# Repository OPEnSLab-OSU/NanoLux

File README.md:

# Nanolux
Cymaspace [Audiolux](https://www.cymaspace.org/audiolux/) Opensource code

The Audiolux device is a product developed by Portland-based company CymaSpace that visualizes music or other performing arts on LED strips, enabling the deaf and hard of hearing to participate in these events. The Audiolux device is a pre-existing product, so the goal of this project is to make improvements such as adding user configurable modes, increasing the number of visualization patterns on the LEDs, making configuration wireless, and improving accuracy of pitch detection.

#### Please check out our [Wiki](https://github.com/OPEnSLab-OSU/Nanolux/wiki) for more user info and documentation.

# Install the Arduino Desktop IDE
Dev environment:
* To get step-by-step instructions select one of the following link accordingly to your operating system.

Windows (http://docs.arduino.cc/software/ide-v1/tutorials/Windows)

Mac OS (http://docs.arduino.cc/software/ide-v1/tutorials/macOS)

Linux (http://docs.arduino.cc/software/ide-v1/tutorials/Linux)

## Dependencies

### 1. Using the **`dependencies`** branch (Recommended)
We have bundled all of the manually required libraries into a single `libraries/` folder on the **`dependencies`** branch. That way, you don’t have to install each one by hand. See the next section if you want/need to manually install them.

1. **Clone (or fetch) the repo and switch to `dependencies`:**
   ```bash
   git clone https://github.com/OPEnSLab-OSU/Nanolux.git
   cd Nanolux
   git fetch origin
   git checkout dependencies
   ```
2. **Locate the `libraries/` folder** at the root of this branch. It contains:
   - ESPAsyncWebServer (v1.2.3)
   - AsyncTCP (v1.1.4)
   - AudioPrism
   - All other custom or manually‑required libraries as seen in the next section
3. **Copy (or symlink) that `libraries/` folder into your Arduino sketchbook’s “libraries” directory.**  
   - On Windows, your sketchbook is usually:  
     ```
     C:\Users\<YourUserName>\Documents\Arduino\libraries
     ```
   - On macOS/Linux, it’s typically:  
     ```
     ~/Arduino/libraries
     ```
   For example:
   ```bash
   # if your sketchbook is ~/Arduino
   cp -r libraries ~/Arduino/
   ```

   Once that’s done, Arduino IDE will automatically pick up those libraries the next time you open it.

4. **Switch back to `main` (if you want to compile/upload the main firmware):**
   ```bash
   git checkout main
   ```
   Because your `main/` folder references those libraries by name, Arduino can now find them.

### 2. Installing via Arduino IDE / Library Manager (Alternate)
You will also need several libraries. See the [IDE Setup Guide](https://github.com/OPEnSLab-OSU/Nanolux/wiki/Arduino-IDE-Setting-Guide) Wiki Page for steps on how to install these libraries.

- Ai ESP32 Rotary Encoder (1.6)
- ArduinoJson (7.1.0)
- FastLED (3.7.0)
- fast4ier (1.0.0)
- ESP32 Board Library (2.0.17)

All dependencies above are installable through the Library Manager of the Arduino IDE, or with the 
[Arduino CLI](https://arduino.github.io/arduino-cli/0.28/) tool.

The following dependencies must be installed manually. Refer to Wiki for more info.

* ESPAsynWebServer (1.2.3): https://github.com/me-no-dev/ESPAsyncWebServer
* AsyncTCP (1.1.4): https://github.com/me-no-dev/AsyncTCP
* AudioPrism: https://github.com/udellc/AudioPrism

# Install Board
You will need to install the ESP32 board driver for developing on this board.
* Install ESP32 Board: https://www.hackster.io/abdularbi17/how-to-install-esp32-board-in-arduino-ide-1cd571
You will also need to check the port connection with ESP32 Board.
* Serial Connection with ESP32: https://docs.espressif.com/projects/esp-idf/en/latest/esp32/get-started/establish-serial-connection.html

Use the “ESP32” package by Espressif Systems at version 2.0.16. In Arduino IDE, open Tools → Board → Boards Manager, search for “esp32,” and install or roll back to esp32 by Espressif Systems v2.0.16. This version is required to compile FastLED 3.7.0 without errors.

# Using the AudioLux Device
Once the device is set up correctly, it can be powered on using its micro USB and fed audio through the 3.5mm audio jack. To configure the device, either use the rotary encoder to cycle through patterns and modes or use the AudioLux web app (ensure the web application is deployed by following these steps in the Wiki: [The Web App](https://github.com/OPEnSLab-OSU/Nanolux/wiki/The-Web-App)). Once deployed by the device, the web app can be connected to by opening your device's Wifi settings and selecting the AudioLux Wifi (`AudioluxUnsecured`) that is hosted by the AudioLux device, and then opening the web app by going to `http://192.168.4.1/` if the device has not been configured before or `http://audiolux.local` if the device has been configured. Once connected, the AudioLux device can be configured freely using all of the web app's functionality and/or the device's rotary encoder.

# Some Important Things To Note

1. The most up to date stable release is located in the [Main](https://github.com/OPEnSLab-OSU/Nanolux/tree/main/main) directory. 
This is the code that should be uploaded to the device. Make sure to follow the Web App Wiki to upload the code
needed to run the Web App.

2. If you wish to disable the webapp, you can comment out the flag "ENABLE_WEB_SERVER". Make note to which analog ports are being used,
disabling the webapp however should not give a boost in performance, given that the webapp is asynch and on a seperate core.

---

# Contributors
2021-2022 Team:

John Zontos (zontosj@oregonstate.edu)

Evan Cochran (cochraev@oregonstate.edu)

Longjie Guan (guanl@oregonstate.edu)

Ming Wei (weimi@oregonstate.edu)

2022-2023 Team:

Andrew Gingerich (gingeria@oregonstate.edu)

Luke Goldsworthy (goldswol@oregonstate.edu)

Mac Handley (handlem@oregonstate.edu)

Vishnu Kalidas (kalidasv@oregonstate.edu)

Jorden Mortenson (mortejor@oregonstate.edu)

David Mora (morad@oregonstate.edu)

2023-2024 Team:

Andrew Adisoemarta (adisoema@oregonstate.edu)

Anshul Batish (batisha@oregonstate.edu)

Caleb Shilling (shillinc@oregonstate.edu)

Can Yang (yangca@oregonstate.edu)

Scout Hawkey (hawkeys@oregonstate.edu)

2024-2025 Team:

Andrew Craeton (craetona@oregonstate.edu)

Theodore Ngo (ngoth@oregonstate.edu)

Matthew Manuguid (manuguim@oregonstate.edu)

Nicholas Wooldridge (wooldrni@oregonstate.edu)

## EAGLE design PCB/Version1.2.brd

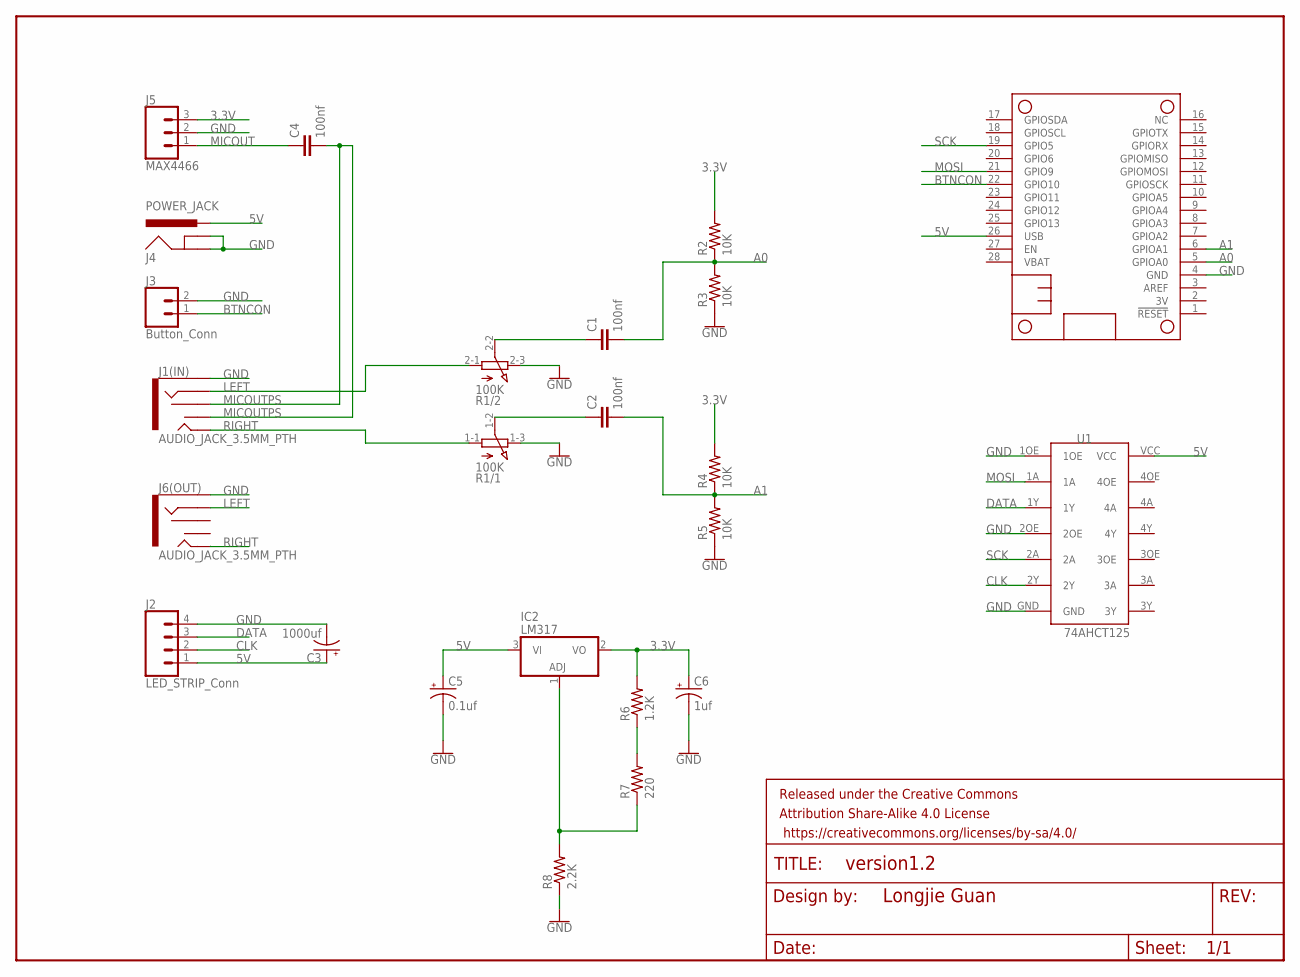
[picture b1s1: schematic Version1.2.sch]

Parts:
C1, C2, C4: 100nf; C2.5-2
C3: 1000uf; B45181A
C5: 0.1uf; B45181A
C6: 1uf; B45181A
FRAME1: FRAME-LETTERNO_PACKAGE; DUMMY
IC2: LM317; TO220H
J1(IN), J6(OUT): AUDIO_JACK_3.5MM_PTH; AUDIO-JACK
J2: LED_STRIP_Conn; 1X04_LOCK
J3: Button_Conn; 1X02
J4: POWER_JACK; POWER_JACK_PTH
J5: MAX4466; 1X03
MS1: FEATHERWING_NODIM; FEATHERWING_DIM
R1: 100K; 3RP/1610G
R2, R3, R4, R5: 10K; 0204/7
R6: 1.2K; 0204/7
R7: 220; 0204/7
R8: 2.2K; 0204/7
U1: 74AHCT125; 74AHCT125FP

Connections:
3.3V: C6.+, IC2.2 (VO), J5.3, R2.2, R4.2, R6.2
5V: C3.+, C5.+, IC2.3 (VI), J2.1, J4.PWR, MS1.26 (USB), U1.VCC
A0: C1.2, MS1.5 (GPIOA0), R2.1, R3.2
A1: C2.2, MS1.6 (GPIOA1), R4.1, R5.2
BTNCON: J3.1, MS1.22 (GPIO10)
CLK: J2.2, U1.2Y
DATA: J2.3, U1.1Y
GND: C3.-, C5.-, C6.-, J1(IN).SLEEVE, J2.4, J3.2, J4.GND, J4.GNDBREAK, J5.2, J6(OUT).SLEEVE, MS1.4 (GND), R1.1-3 (E), R1.2-3 (E), R3.1, R5.1, R8.1, U1.1OE, U1.2OE, U1.GND
LEFT: J1(IN).RING, J6(OUT).RING, R1.2-1 (A)
MICOUT: C4.1, J5.1
MICOUTPS: C4.2, J1(IN).RSH, J1(IN).TSH
MOSI: MS1.21 (GPIO9), U1.1A
unnamed: C1.1, R1.2-2 (S)
unnamed: C2.1, R1.1-2 (S)
unnamed: R6.1, R7.2
unnamed: IC2.1 (ADJ), R7.1, R8.2
RIGHT: J1(IN).TIP, J6(OUT).TIP, R1.1-1 (A)
SCK: MS1.19 (GPIO5), U1.2A

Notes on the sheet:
Longjie Guan

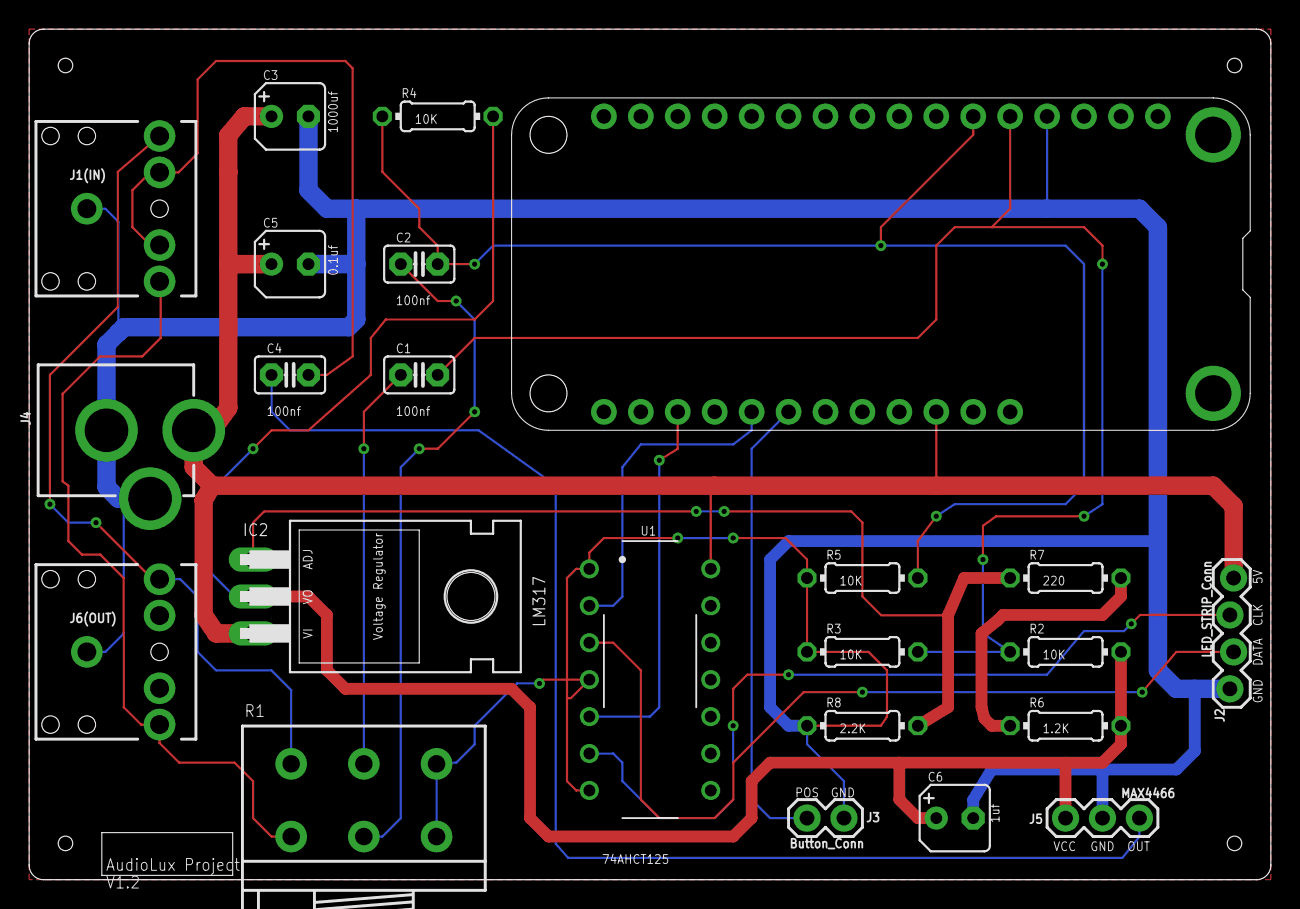
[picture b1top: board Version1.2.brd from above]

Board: 2 copper layers, 85.4 x 58.5 mm, 24 parts (0 on the bottom side), 18 nets.

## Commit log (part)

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2023-12-07 check in
2023-12-07 Save selector UI functional
2023-12-08 Pattern saving complete, web app fixes
2023-12-08 Bugfix: fastLED.clear calls replaced in patterns.cpp with clearLEDSegment()
2023-12-10 Revert "Revert "Merge branch 'simulator' into 2.1.0_unstable""
    This reverts commit 2b6c89d82d19b7e44578e273b65ad534119fa39b.
2023-12-10 Manual merge of previous Simulator branch push
2023-12-11 Fixed strip stopping after 2 seconds
    Added sanity check that pix and vol position does not go over NUM_LEDS
2023-12-13 Simulator readme revision
2023-12-15 Changes to echo ripple
    New todos:
    1. make it asynch with an FSM
    2. get audio jack from home to get the colors and distance working according to the music
2023-12-20 Added the ability to reset saved patterns using the device momentary switch.
2023-12-23 Added the ability to change the smoothing constant and brightness on the web app.
2024-01-09 temp push to work elsewhere.
2024-01-19 formant colors + blending
    Added color blend to the ripples when they collide
2024-01-19 colorful blend
    added changes so that less white is seen when blending/expanding
2024-01-19 modifies
2024-01-19 Added the ability to change the LED strip length on the UI and began fixing issue with UI not updating on occasion.
2024-01-24 added bg pic & changed CSS
2024-01-25 Fixed config data not saving to NVS
2024-02-01 Pattern functions now have paramenters for pattern history pointer and # of addressed LEDs.
2024-02-01 Fixed simulator using the non-smoothed output buffer and moved sim output to after smoothing calculation.
2024-02-02 echo ripple debugging
    testing fixes to implement a new echo ripple into unstable
2024-02-07 check-in
2024-02-08 check-in, laptop-desktop merge
2024-02-08 functional strip splitting
2024-02-09 Style changed
2024-02-10 Update mockapi_dqm_audioluxmockapi.yml
    Added autoformatting action
2024-02-10 Create clang_autoformat.yml
    added clang to a separate workflow
2024-02-10 Update clang_autoformat.yml
    fix to source files in format action
2024-02-10 added to gitignore
2024-02-10 updated clang action
2024-02-13 Brightness and smoothing per-subpattern reimplemented. Fixed bug with getting current subpattern data correctly.
2024-02-14 Monday check-in commit
2024-02-15 6 Major Pattern Functions
    Completed implementation in main, patterns.cpp/h, storage accessing work in progress NOT TESTED
2024-02-16 pattern header file changes
2024-02-16 Feature parity with unstable
2024-02-22 Updated UI CSS
2024-02-22 processDirection function implemented NOTTESTED
    need to add sanity checks
2024-02-23 updtas
2024-02-23 Compile fixes
2024-02-23 Compilation fix
2024-02-26 Added bound checking to API inputs and pattern loading/saving. Untested.
2024-02-27 Bugfixes for byte bounding function parameters and verified manual control mode
2024-03-01 Finished up tug of war functions
    Added volume and frequency tug of war
2024-03-01 Bugfixes and Doxygen comments
2024-03-06 Compile fixes
    Compiles now yay
2024-03-06 Added drop down for config selector.
2024-03-08 quick push
    new fhue and vbrightness
2024-03-08 Tug o' war and Raindrop patterns
    Added two new patterns with variations on the Tug O' War pattern
2024-03-14 Added API calls to change device name and password, added capability to rename device through serial
2024-03-15 Added SSID and password resetting
2024-04-08 Updated documentation
2024-04-08 empty commit, ready for pages
2024-04-08 doxygen manual test
2024-04-08 check-in commit
2024-04-15 Additional docs added
2024-04-15 Adding html page to perform automatic redirection to docs page.
2024-04-19 Doxygen build test
2024-04-19 doxyfile path fix
2024-04-19 deploy: f7f140341c393304e3905966bd094f25c675b375
2024-04-26 Minor update to force pages update
2024-04-26 deploy: f95bdb87bdc83ba005b5b226671c5cdfb19960b8
2024-04-26 deploy: a34a3394f9fe11a0b3b479002ac79991e03a6701
2024-04-26 attempted doxygen update
2024-04-26 deploy: 1f20743fa51dfe23f257cb24146e107d81bc3ecc
2024-04-29 Web app doxyfile and docs changes
2024-04-29 multi-docs attempt 2
2024-04-29 Removed double checkout in Actions
2024-04-29 Removed extra deploy
2024-04-29 deploy: 891d87bd7f26f0a0c6fc35927c7b88b2c140e968
2024-04-29 deploy: 1fdf2683764086d5ef4cc9a97251e66e11246d3e
2024-04-29 deploy: 5cd4fd70c269af92dc06b0410e0ca24ca34fd8b7
2024-05-06 Initial project renaming commit
2024-05-06 Alpha manual pushed, direction feedback needed
2024-05-08 Added a new subpattern data option for postprocessing effects.
2024-05-10 added rotary encoder code
2024-05-10 Working Code
2024-05-10 Web app doxygen fixes
2024-05-12 deploy: e8e0d4384e4ef1c7ed0590510e6288174414762e
2024-05-12 Modified postprocessing effects to use an integer instead of a boolean
2024-05-13 Bigfixes, ready to merge to prerelease
2024-05-13 rotaryEncoder
2024-05-13 deploy: d6877395646266dfd1e3029916e6b487dff88454
2024-05-13 deploy: ebc9a2d244259ce48ddf4b7392078a4b47fdd68e
2024-05-13 deploy: a6ec5bcd6b86a8b0d4232526484bcb968ff37591
2024-05-17 Create file
2024-05-17 Revert "Merge branch '3.0.0_prerelease' of https://github.com/OPEnSLab-OSU/Nanolux into 3.0.0_prerelease"
    This reverts commit a6a5350838db440ca9f1dd9ba14bd06c03140976, reversing
    changes made to 9996c730e3e58d8137f5343e3fc6eb7463fdb04b.
2024-05-17 deploy: 2194b1bccd1e08740f93f9c4c0dee63de07fb0f3
2024-05-17 deploy: b877bdbfc1859840259719a0bf2cd152b2a3f58a
2024-05-17 deploy: 0cfd07c08b23ac1bc4633db8edc3a45a4ca2ee18
2024-05-17 removed extra deploy steps
2024-05-18 Added landing page and moved old folders to "archive" before potential removal
2024-05-18 deploy: 99b6abca77e2158ae7b82c3f0a7f0a978e1e1e91
2024-05-18 deploy: e185ffc2e5fda6504a0ad0fb1dd6f5dba0a2bf60
2024-05-18 deploy: 60f0ad9f57ea9af17fa63f838cdf462b4ce79a50
2024-05-20 Re-implemented manual mode, temporary crash prevention on bands pattern
2024-05-20 Ready for merge.
2024-05-20 deploy: 54ab0f8d7db833eef20664a577c1daba0a8f55ad
2024-05-20 Uploading manual files
2024-05-20 vowel detection
    Added vowel detection to the newest prerelease
2024-05-20 saturated and groovy fix *not tested*
2024-05-22 Manual 1.0 release, additional manual pages, manual build script, new Bar Fill pattern
2024-05-23 updated vowel detection
    ^
2024-05-23 removed/updated old comment
2024-05-24 Fixed postprocess being a boolean
2024-05-24 deploy: 9156750487f472cc3ad2036702db24e92c02540c
2024-05-24 deploy: d7d0fa99a73f935e9fb425e4dc48de33d1a4a4d5
2024-05-24 deploy: 5c711aad61e23256cfecdc3031a9d13b91ac99e4
2024-05-24 Current pattern on UI now decreases when the viewed one is removed
2024-05-25 Minor docs changes, removal of old functions
2024-05-25 deploy: 088f2dd2dadbc42a36791ff2c95bc1a1d40bfd2e
2024-05-27 deploy: bc0de6fb54247915f35cd535bd10570d5aeff467
2024-06-02 deploy: 52b1d48014b2c4b3f8da646af4b15aae977b8ed4
2024-06-02 Added clean command to npm
2024-06-02 Update README.md
    Added the 2023-2024 dev team
2024-06-02 deploy: ac50dacd284c3b173ce7d6e379cd1e72cebf2b9f
2024-06-02 deploy: 390a1d530bc5f03b499299107de0e72f9bbf62bb
2024-06-24 Fixes to software AP mDNS, expanded smoothing range, simplified postprocessing mode selection
2024-06-26 Fix to rotary encoder, removed encoder button calls
2024-06-28 Disabled SD Loader by default
2024-06-29 deploy: 777058139534b63654c534eac946d8d599dfe89c
2024-07-29 Simulator V3 Prerelease
2024-12-04 Adjusted rotary encoder upper boundary and removed modulo logic due to redundancy
2024-12-04 modified core analysis to demo audioprism integration
2025-01-29 core_analysis functions replaced by audioprism modules
2025-01-30 Added functionality and logic for encoder bidirectionality with web app
2025-01-31 ensureing audio analysis files compile
2025-02-05 enabled SD card and added print statements to debug encoder value updates
2025-02-19 fully implemented bidirectional communication from encoder to pattern selection UI in webapp
2025-02-27 pattern_test
2025-02-28 correcting type issues in legacy code
2025-02-28 Commit to prep for adding new patterns
2025-02-28 fix to previous commit
2025-02-28 note testing
2025-02-28 note fixes
2025-03-07 Added noteEQ pattern
2025-03-07 optimized and fixed noteEQ
2025-03-07 Improvements to synesthesia fading
2025-03-07 Fixed delta functionality
2025-03-11 Added rainbow slider and modified patterns component
2025-03-11 modified css file for multirange slider component
2025-04-15 Removal of rainbow slider from pattern_settings, modified rainbow slider component, adjusted all settings components to include tooltips, added new dependency to project
2025-04-15 updated spacing, multi-range-slider dependency, color palette, and deleted redundant css files
2025-04-15 readded padding-top to main app
2025-04-22 Modified CSS for Settings page components to increase sizing, align color schemes, and space elements properly
2025-04-25 verified multi window analysis functions functionality
2025-04-26 transistioned to new analysis loop in patterns. deleted previous AA files
2025-05-02 styled wifi page to match settings page and swapped the config imported dropdown with a select element to style it the same as current pattern
2025-05-06 implemented UI color themes and a toggle for basic/advanced settings page
2025-05-09 Modified settings index.js files
2025-05-13 ensure loaded_pattern attributes from rotary encoder stay uint64
2025-05-16 Added 2024-2025 team to README.md
2025-05-16 deploy: c1efa2eded04c2b0ad85c92a57e05226867cde0c
2025-05-20 styled tooltip popups, added tooltips to SimpleChooser options, adjusted tooltip descriptions, refactored and restyled pattern modal for future dev
2025-05-24 fully removed manual_pattern and VERSION_2_HARDWARE and LittleFS macro logic
2025-05-24 moved to fast4ier
2025-05-24 fixed type issues casued by mergeing new patterns
2025-05-24 deploy: 06f1993747c40e9596c4e4d5e0e46a08c346d2fc
2025-05-25 Update README.md
    Added End-User Instructions
2025-05-27 added screen reader compatibility with ARIA
2025-05-27 updated size-plugin.json from npm run build
2025-05-28 testing changes to fft loop
2025-05-28 changes verified - FTT works
2025-05-28 simplified AP init
2025-05-30 resolved lint and Lighthouse issues
2025-05-30 add GitHub actions for ESLint a11y and Lighthouse CI
2025-05-30 remove Windows-only clean script from Lighthouse config and update Node version in GitHub Actions
2025-05-30 modified GitHub actions scope for lighthouse and lint to only run on changes inside WebApp
2025-05-31 deploy: 5660dfe0f4278995971c82eab45bc783ff898829
2025-06-01 updated markdown files for frontend and rotary encoder changes
2025-06-01 fixed comment typo in loop()
2025-06-01 updated/ added jsdoc comments to new and modified components for doxygen build
2025-06-01 update doxygen to grant write permissions
2025-06-01 removed running doxygen on PRs (no write permissions)
2025-06-01 added optional categories to the lighthouse config
2025-06-01 deploy: 3693334008dcbd6e2af82f7976f0607575dc1d45
2025-06-01 increased analysis functionality
2025-06-02 analysis changes
2025-06-02 added doxygen comments
2025-06-02 deploy: 3b99eec53f2a7612261ea4c06b92398f448320fd
2025-06-02 removed old dependency reference
2025-06-02 deploy: 217a24fe27d7673510b43eb8aaadfb9acbe763a7
2025-06-02 deploy: 557227b24b2b495f88e7c3a4f2abd4c7d14edb8a
2025-06-02 deploy: 75d62b045dcc17e12eb549a0f80dd202f4e35e2a
2025-06-02 deploy: 82866e60f4b0b35700e8b83d6bafccb4b726d636
2025-06-02 deploy: 66bee14ed602e39b77d9191e75f7a00f12de28fd
2025-06-02 hopefully this is good
2025-06-03 modified the drop down config menu and pattern order
2025-06-03 fixed bug
2025-06-03 fixed pattern model
2025-06-04 deploy: 9305c9fc801d70f97009524b27920a01fe5f534e
2025-06-04 fixed network modal, redirect modal, and wifi selector styling to work with themes
2025-06-04 another typo in the README
2025-06-04 restored min/max hue
2025-06-04 deploy: bddeb306306dc9c1e37994db58f84c1cf69803f5
2025-06-06 hue fix
2025-06-06 deploy: 9c3a2d6cb1f1c0ed5ed3e58421f0bc6bd95ad961

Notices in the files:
parts and their libraries:
SparkFun-Connectors: Licensing: Creative Commons ShareAlike 4.0 International - https://creativecommons.org/licenses/by-sa/4.0
SparkFun-Aesthetics: Released under the Creative Commons Attribution Share-Alike 4.0 License
SparkFun-Aesthetics: https://creativecommons.org/licenses/by-sa/4.0
